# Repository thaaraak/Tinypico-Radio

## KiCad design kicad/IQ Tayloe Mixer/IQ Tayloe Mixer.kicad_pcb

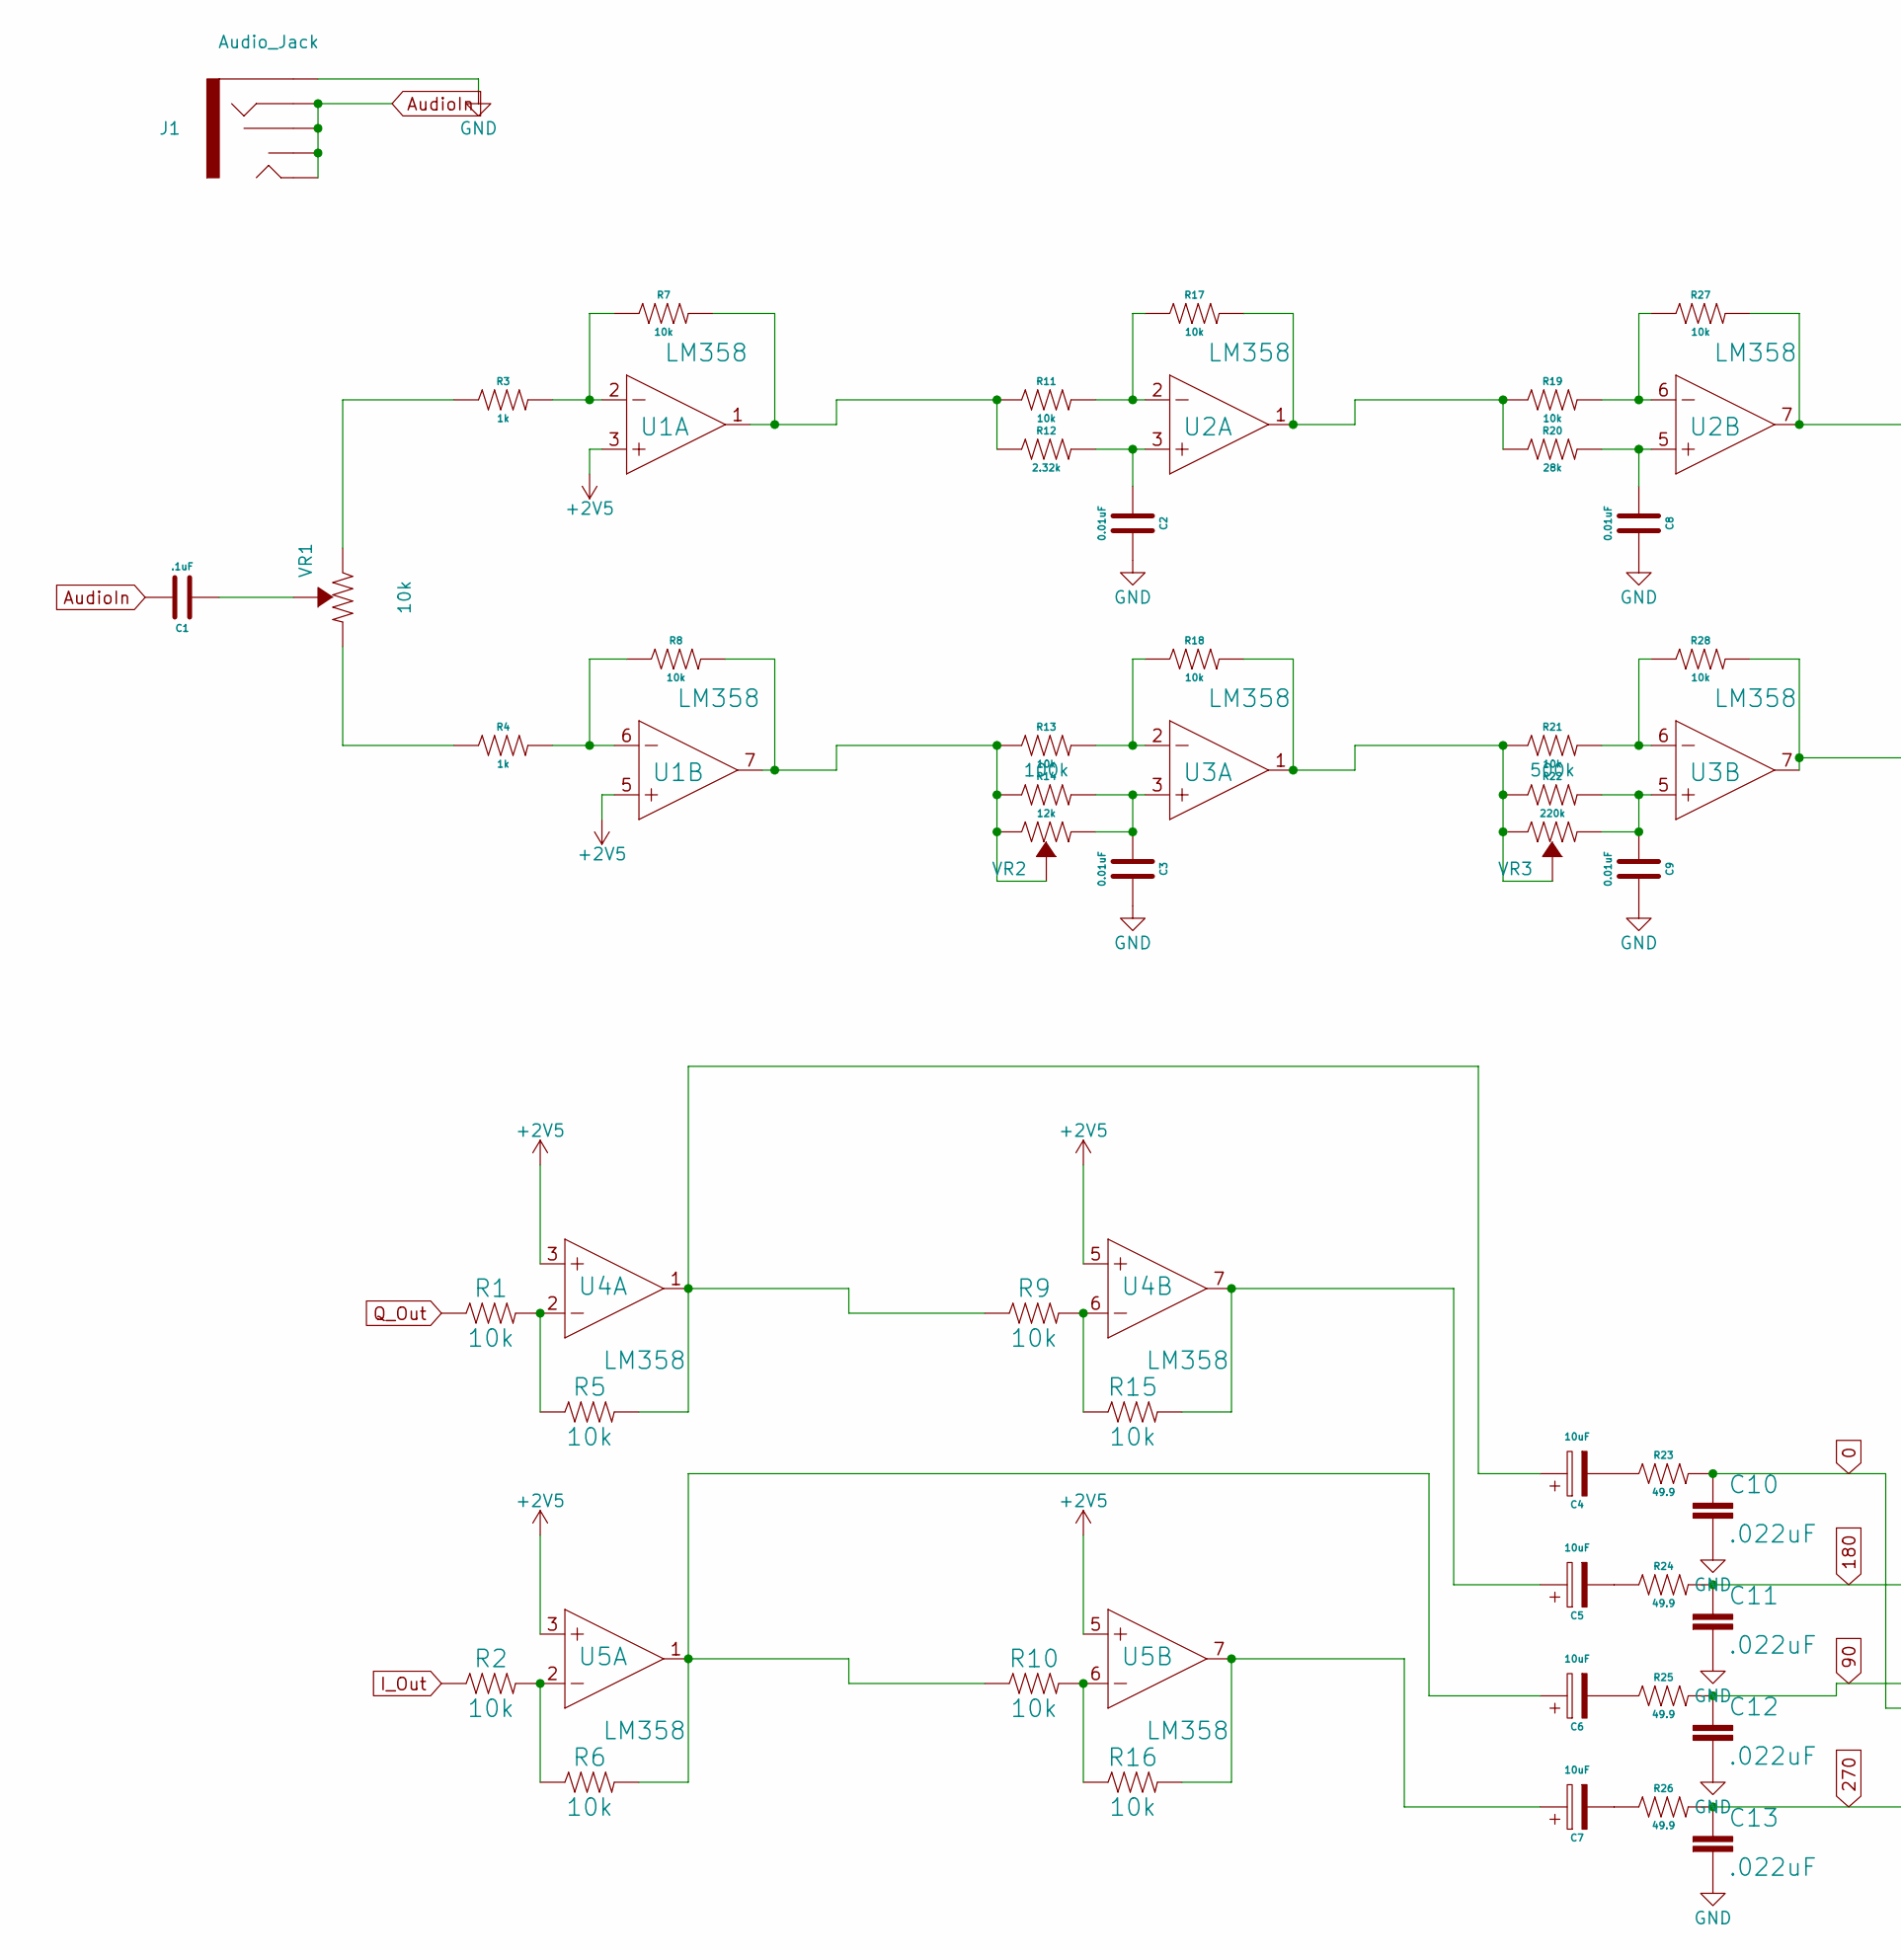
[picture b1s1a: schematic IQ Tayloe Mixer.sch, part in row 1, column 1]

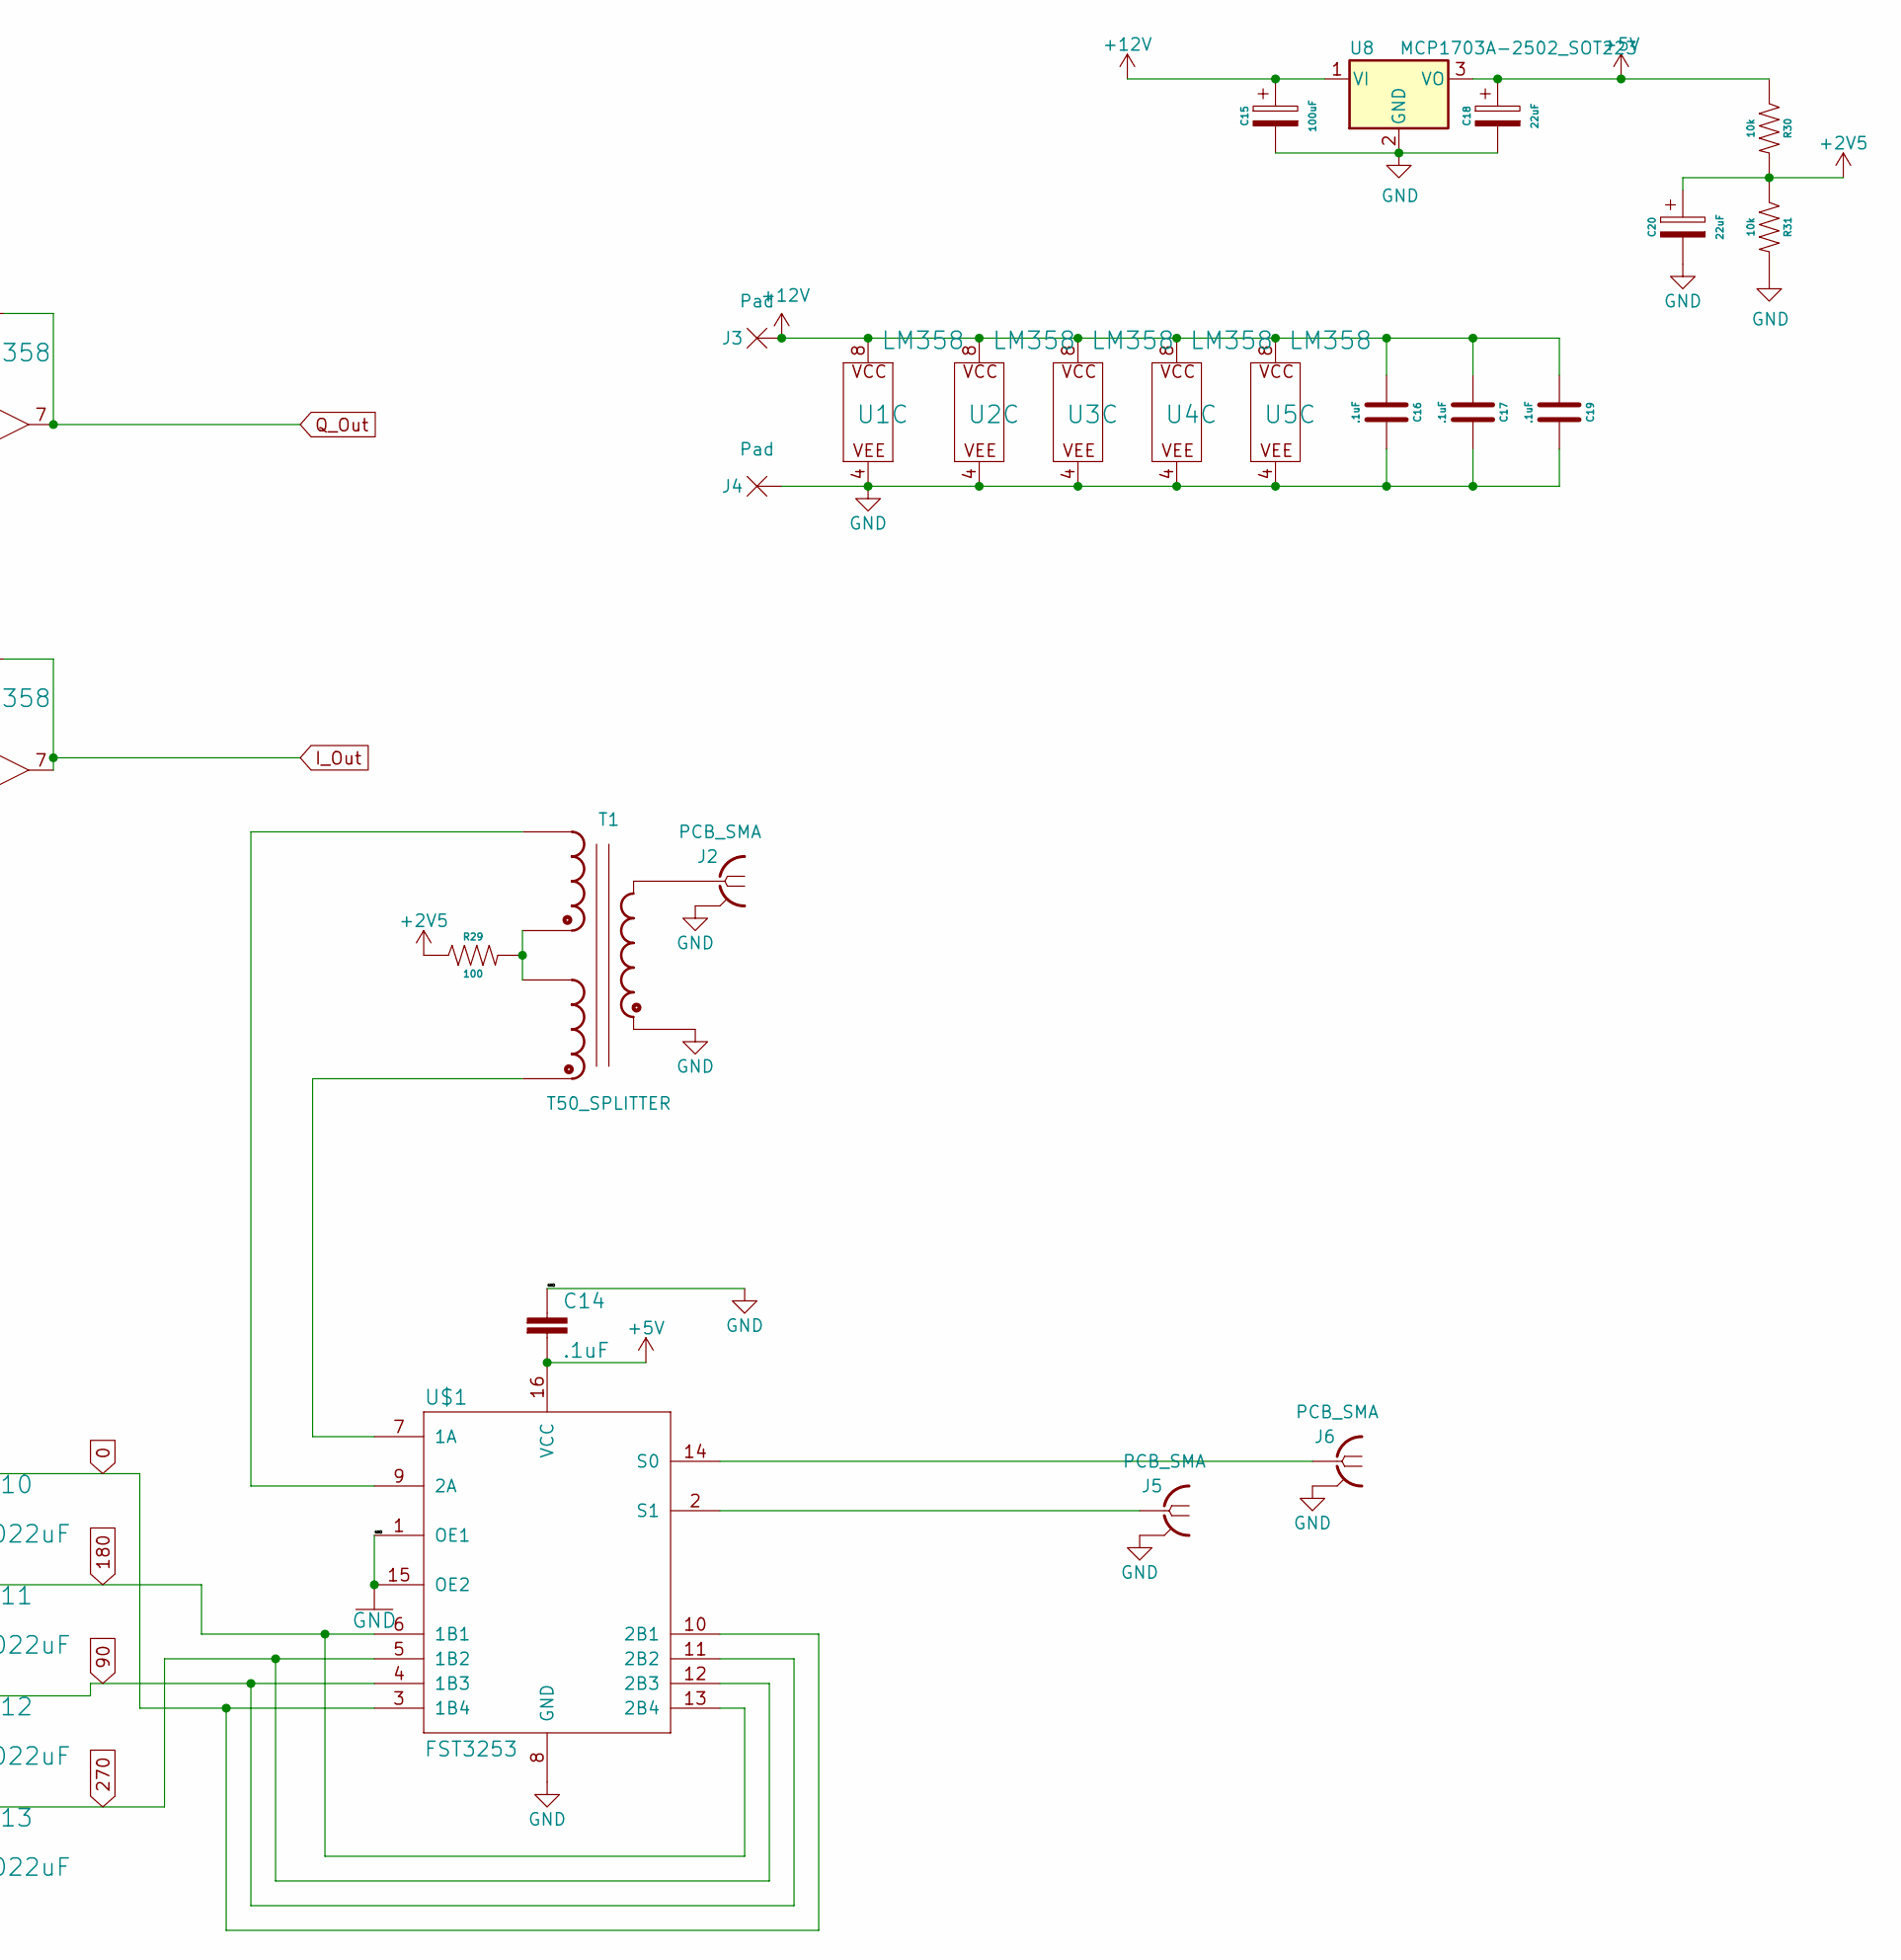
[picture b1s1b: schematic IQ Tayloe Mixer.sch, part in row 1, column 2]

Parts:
C1, C14, C16, C17, C19: .1uF; Capacitor 0805
C2, C3, C8, C9: 0.01uF; Capacitor 0805
C4, C5, C6, C7: 10uF; Cap_4x5.4
C10, C11, C12, C13: .022uF; Capacitor 1206
C15: 100uF; Cap_6.3x5.4
C18, C20: 22uF; Cap_4x5.4
J1: Audio_Jack
J2, J5, J6: PCB_SMA; PCB SMA
J3, J4: Pad
R1, R2, R5, R6, R7, R8, R9, R10, R11, R13, R15, R16, R17, R18, R19, R21, R27, R28, R30, R31: 10k; Resistor 0805
R3, R4: 1k; Resistor 0805
R12: 2.32k; Resistor 0805
R14: 12k; Resistor 0805
R20: 28k; Resistor 0805
R22: 220k; Resistor 0805
R23, R24, R25, R26: 49.9; Resistor 0805
R29: 100; Resistor 0805
T1: T50_SPLITTER; T50 Trifilar
U1, U2, U3, U4, U5: LM358; SO08
U8: MCP1703A-2502_SOT223; TO-252-3_TabPin2
U$1: FST3253; SO16
VR1: 10k; Trimpot
VR2: 100k; Trimpot
VR3: 500k; Trimpot

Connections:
0: C10.1, R23.2, U$1.3 (1B4), U$1.10 (2B1)
90: C12.1, R25.2, U$1.4 (1B3), U$1.11 (2B2)
180: C11.1, R24.2, U$1.6 (1B1), U$1.13 (2B4)
270: C13.1, R26.2, U$1.5 (1B2), U$1.12 (2B3)
+2V5: C20.1, R29.1, R30.2, R31.1, U1.3 (+IN), U1.5 (+IN), U4.3 (+IN), U4.5 (+IN), U5.3 (+IN), U5.5 (+IN)
+5V: C14.2, C18.1, R30.1, U8.3 (VO), U$1.16 (VCC)
+12V: C15.1, C16.1, C17.1, C19.1, J3.1, U1.8 (P$V+), U2.8 (P$V+), U3.8 (P$V+), U4.8 (P$V+), U5.8 (P$V+), U8.1 (VI)
AudioIn: C1.2, J1.RING, J1.RSH, J1.TIP, J1.TSH
GND: C2.2, C3.2, C8.2, C9.2, C10.2, C11.2, C12.2, C13.2, C14.1, C15.2, C16.2, C17.2, C18.2, C19.2, C20.2, J1.SLEEVE, J2.2, J2.3 (2), J2.4 (2), J2.5 (2), J4.1, J5.2, J5.3 (2), J5.4 (2), J5.5 (2), J6.2, J6.3 (2), J6.4 (2), J6.5 (2), R31.2, T1.C1B, U1.4 (P$V-), U2.4 (P$V-), U3.4 (P$V-), U4.4 (P$V-), U5.4 (P$V-), U8.2 (GND), U$1.1 (OE1), U$1.8 (GND), U$1.15 (OE2)
I_Out: R2.1, R28.2, U3.7 (OUT)
unnamed: C1.1, VR1.2 (WIPER)
unnamed: C2.1, R12.2, U2.3 (+IN)
unnamed: C3.1, R14.2, U3.3 (+IN), VR2.3 (CCW)
unnamed: C4.1, R5.2, R9.1, U4.1 (OUT)
unnamed: C4.2, R23.1
unnamed: C5.1, R15.2, U4.7 (OUT)
unnamed: C5.2, R24.1
unnamed: C6.1, R6.2, R10.1, U5.1 (OUT)
unnamed: C6.2, R25.1
unnamed: C7.1, R16.2, U5.7 (OUT)
unnamed: C7.2, R26.1
unnamed: C8.1, R20.2, U2.5 (+IN)
unnamed: C9.1, R22.2, U3.5 (+IN), VR3.3 (CCW)
unnamed: J2.1, T1.C1A
unnamed: J5.1, U$1.2 (S1)
unnamed: J6.1, U$1.14 (S0)
unnamed: R1.2, R5.1, U4.2 (-IN)
unnamed: R2.2, R6.1, U5.2 (-IN)
unnamed: R3.1, VR1.1 (CW)
unnamed: R3.2, R7.1, U1.2 (-IN)
unnamed: R4.1, VR1.3 (CCW)
unnamed: R4.2, R8.1, U1.6 (-IN)
unnamed: R10.2, R16.1, U5.6 (-IN)
unnamed: R7.2, R11.1, R12.1, U1.1 (OUT)
unnamed: R11.2, R17.1, U2.2 (-IN)
unnamed: R8.2, R13.1, R14.1, U1.7 (OUT), VR2.1 (CW), VR2.2 (WIPER)
unnamed: R13.2, R18.1, U3.2 (-IN)
unnamed: R9.2, R15.1, U4.6 (-IN)
unnamed: R17.2, R19.1, R20.1, U2.1 (OUT)
unnamed: R18.2, R21.1, R22.1, U3.1 (OUT), VR3.1 (CW), VR3.2 (WIPER)
unnamed: R19.2, R27.1, U2.6 (-IN)
unnamed: R21.2, R28.1, U3.6 (-IN)
unnamed: R29.2, T1.C2A, T1.C3B
unnamed: T1.C2B, U$1.7 (1A)
unnamed: T1.C3A, U$1.9 (2A)
Q_Out: R1.1, R27.2, U2.7 (OUT)

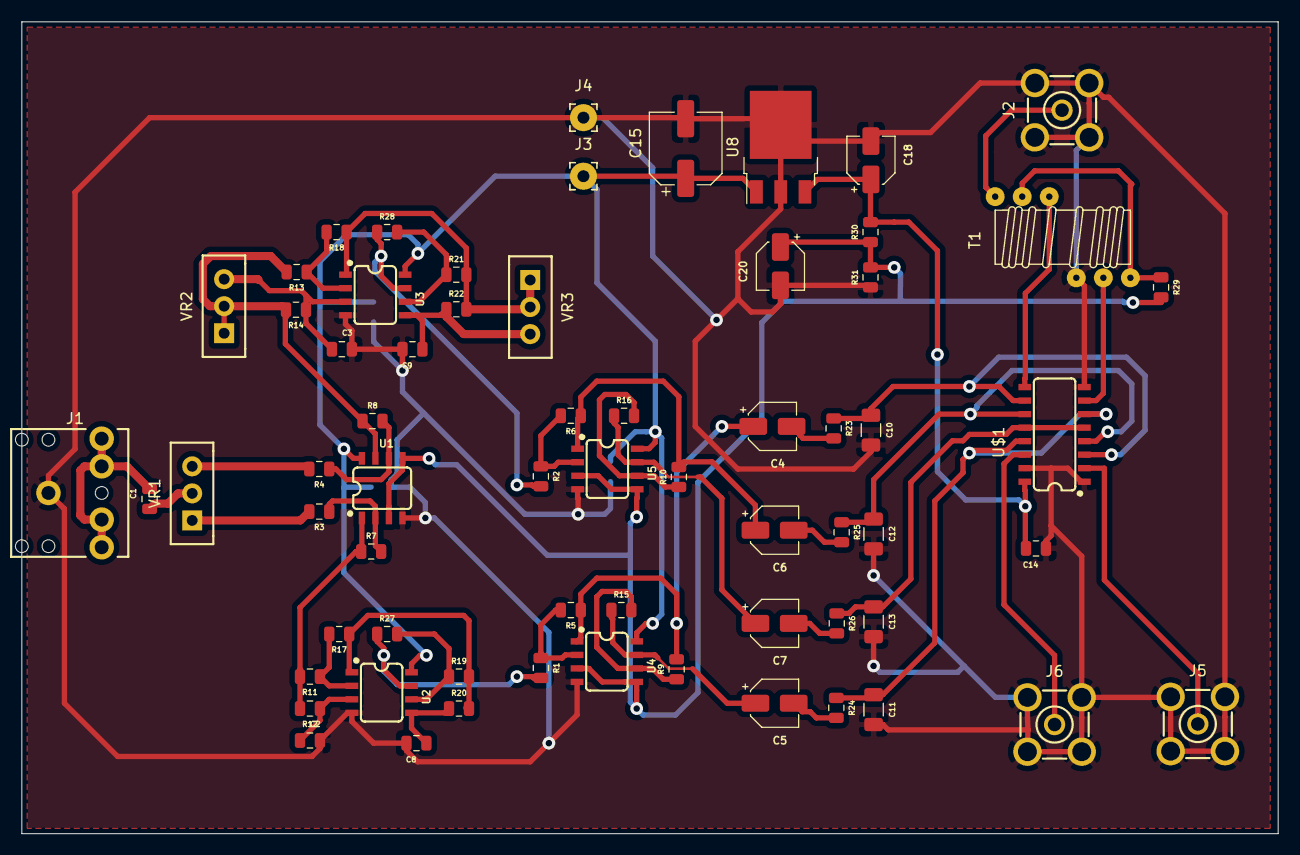
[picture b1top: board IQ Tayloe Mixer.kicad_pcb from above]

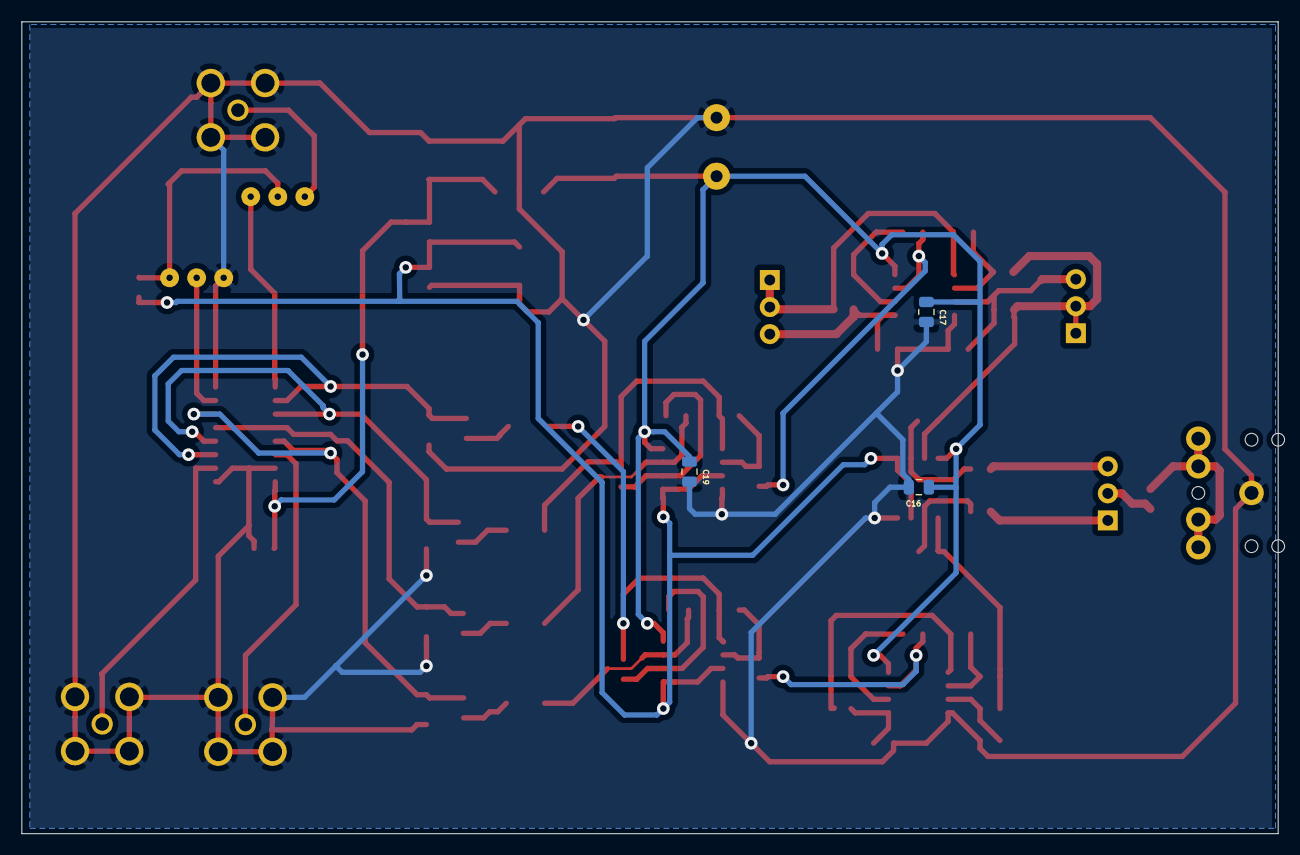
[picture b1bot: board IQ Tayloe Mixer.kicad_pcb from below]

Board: 2 copper layers, 118.0 x 76.2 mm, 68 parts (3 on the bottom side), 46 nets.

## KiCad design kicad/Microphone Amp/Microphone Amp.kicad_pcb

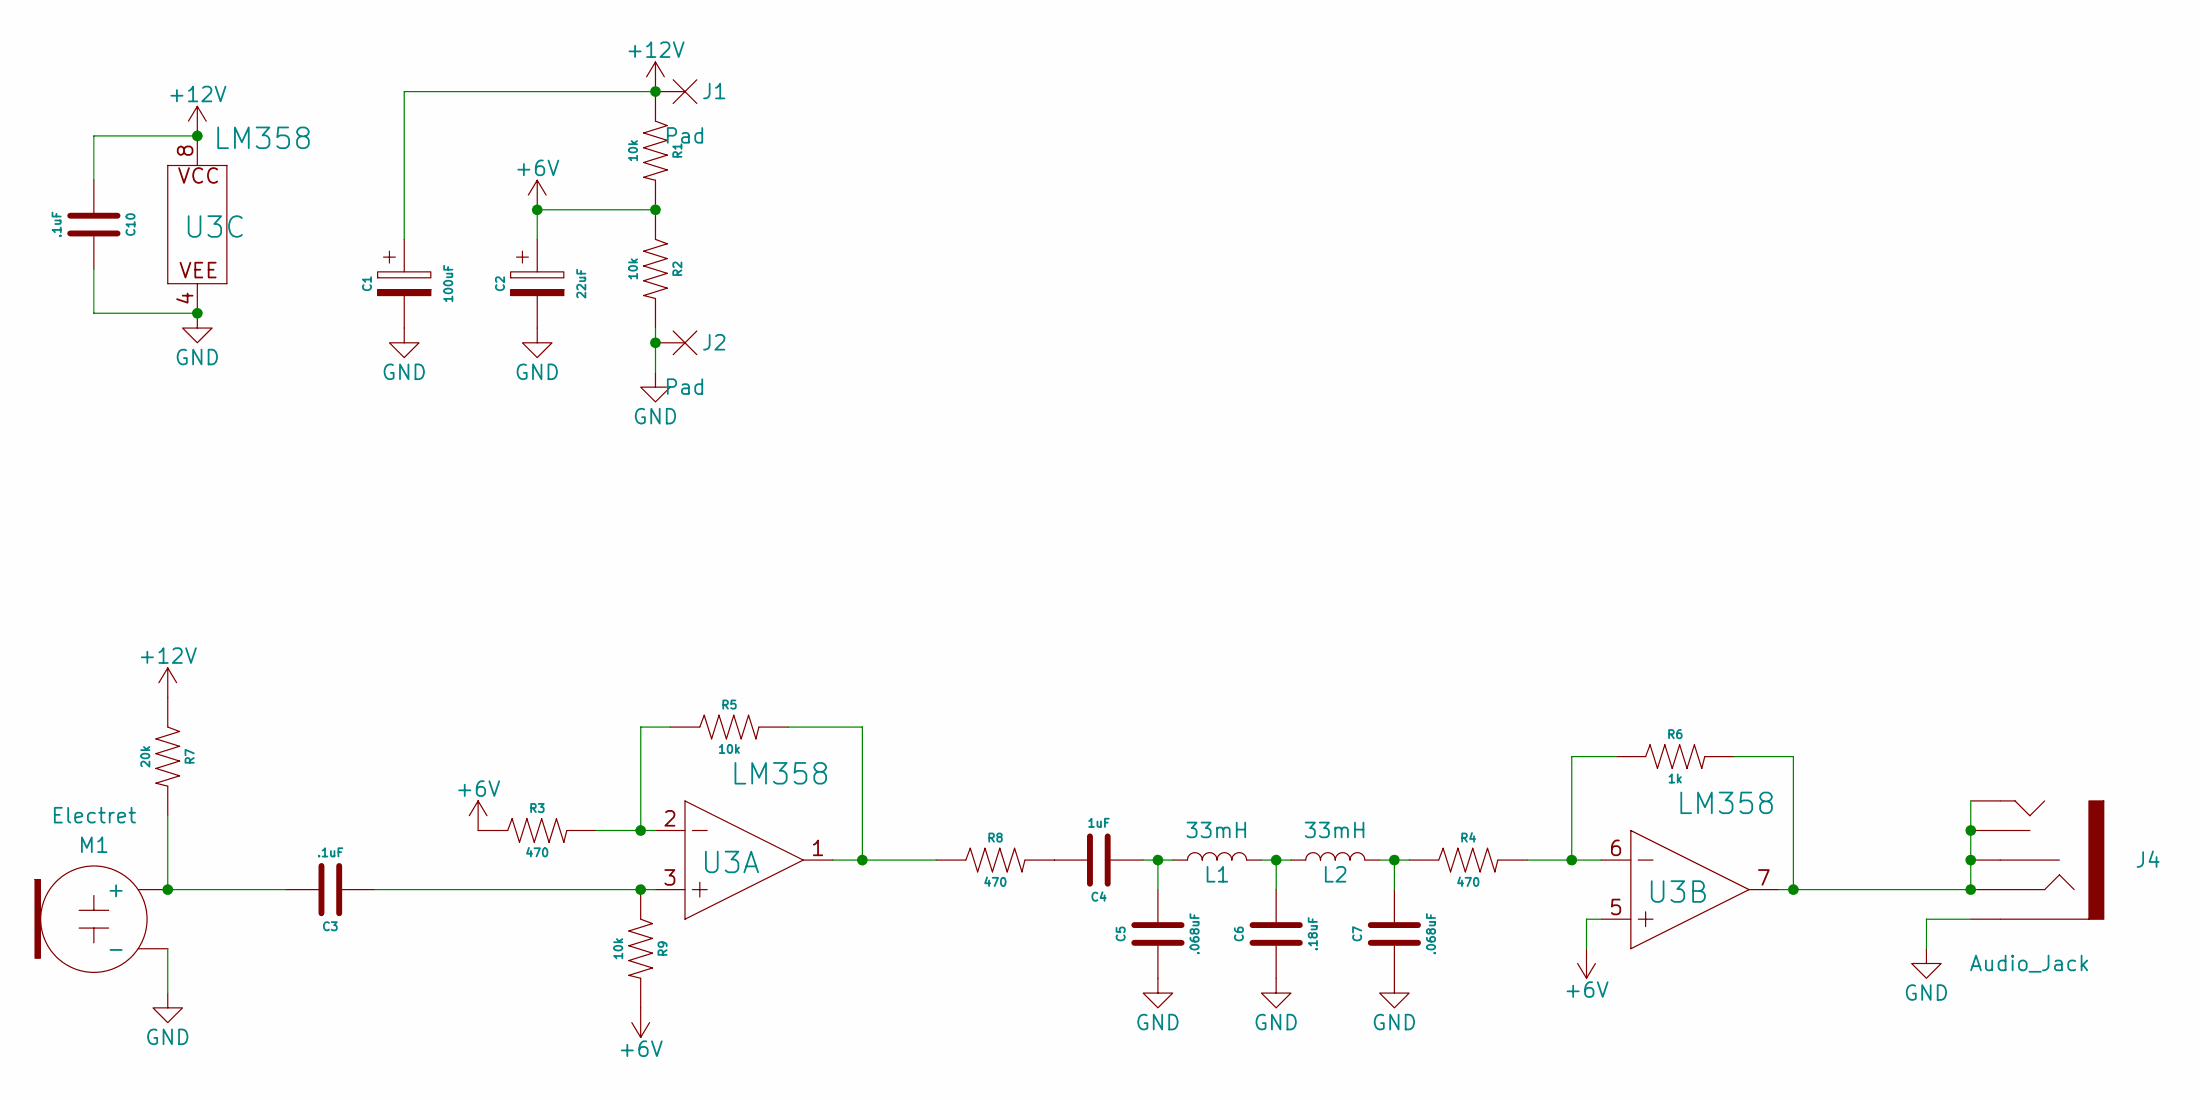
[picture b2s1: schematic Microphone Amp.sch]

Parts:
C1: 100uF; Cap_6.3x5.4
C2: 22uF; Cap_4x5.4
C3, C10: .1uF; Capacitor 0805
C4: 1uF; Capacitor 0805
C5, C7: .068uF; Capacitor 1206
C6: .18uF; Capacitor 1206
J1, J2: Pad
J4: Audio_Jack
L1, L2: 33mH; Inductor_5mm
M1: Electret
R1, R2, R5, R9: 10k; Resistor 0805
R3, R4, R8: 470; Resistor 0805
R6: 1k; Resistor 0805
R7: 20k; Resistor 0805
U3: LM358; SO08

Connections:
+6V: C2.1, R1.2, R2.1, R3.1, R9.2, U3.5 (+IN)
+12V: C1.1, C10.1, J1.1, R1.1, R7.1, U3.8 (P$V+)
GND: C1.2, C2.2, C5.1, C6.1, C7.1, C10.2, J2.1, J4.SLEEVE, M1.2 (-), R2.2, U3.4 (P$V-)
unnamed: C3.1, R9.1, U3.3 (+IN)
unnamed: C3.2, M1.1 (+), R7.2
unnamed: C4.1, C5.2, L1.1
unnamed: C4.2, R8.2
unnamed: C6.2, L1.2, L2.1
unnamed: C7.2, L2.2, R4.1
unnamed: J4.RING, J4.RSH, J4.TIP, J4.TSH, R6.2, U3.7 (OUT)
unnamed: R3.2, R5.1, U3.2 (-IN)
unnamed: R4.2, R6.1, U3.6 (-IN)
unnamed: R5.2, R8.1, U3.1 (OUT)

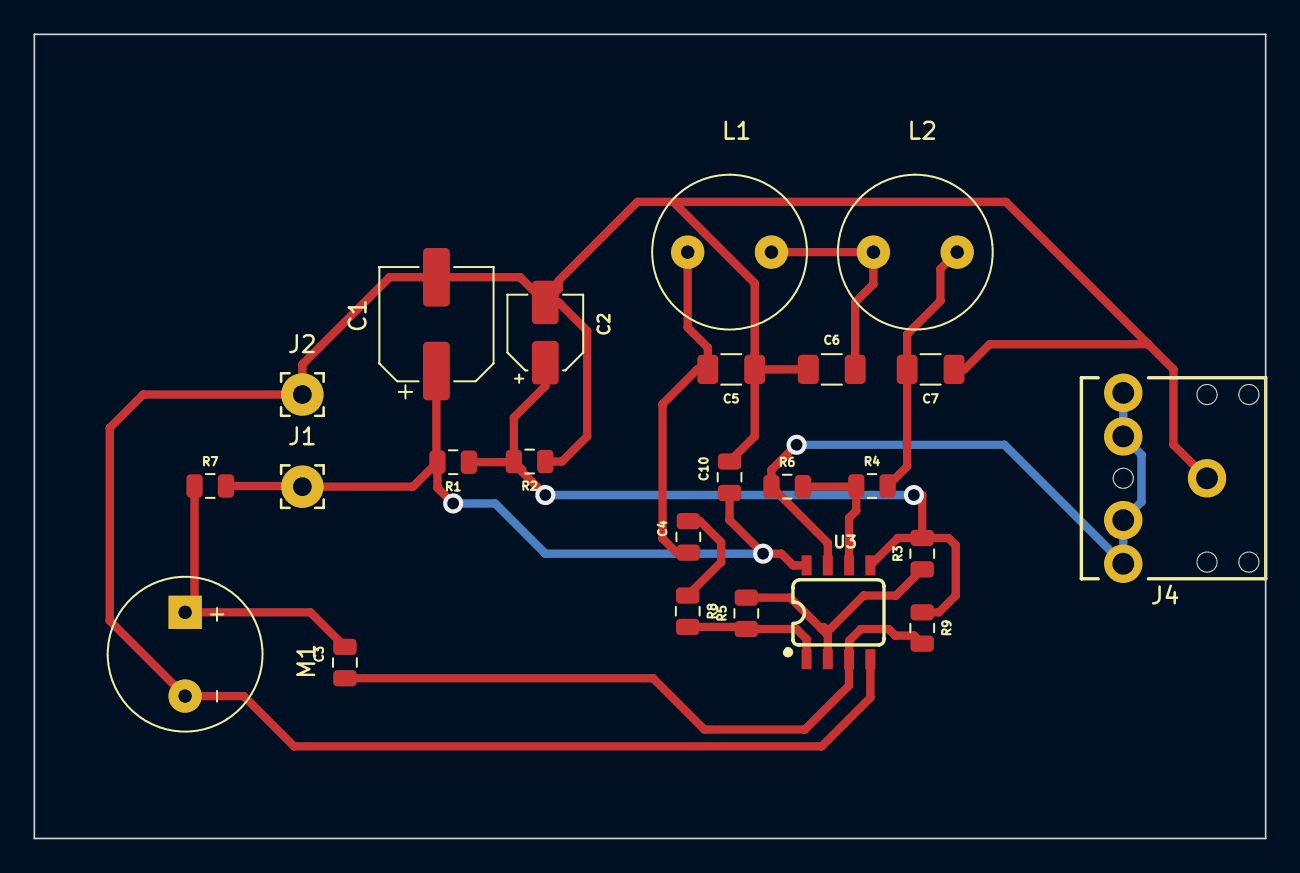
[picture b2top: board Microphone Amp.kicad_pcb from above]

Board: 2 copper layers, 73.5 x 48.0 mm, 24 parts (0 on the bottom side), 13 nets.

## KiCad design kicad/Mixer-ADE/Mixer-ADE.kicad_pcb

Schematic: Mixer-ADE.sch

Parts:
C1, C2: 100uF; CPOL-RADIAL-2.5MM-5MM
C3, C5: 1uF; CAP-PTH-5MM
C4, C10: 47nF; CAP-PTH-5MM
C6, C7: 680nF; CAP-PTH-5MM
C8, C9: 220pF; CAP-PTH-5MM
J1: Audio_Jack
J2, J3, J6: BNC
M1, M2: ADEX-10L
R1, R8: 51; R_Axial_DIN0204_L3.6mm_D1.6mm_P2.54mm_Vertical
R2, R15: 3.3k; R_Axial_DIN0204_L3.6mm_D1.6mm_P2.54mm_Vertical
R3, R4: 50; R_Axial_DIN0204_L3.6mm_D1.6mm_P2.54mm_Vertical
R5: 100; R_Axial_DIN0204_L3.6mm_D1.6mm_P2.54mm_Vertical
R6, R7: 47; R_Axial_DIN0204_L3.6mm_D1.6mm_P2.54mm_Vertical
R9, R10, R13, R14: 150; R_Axial_DIN0204_L3.6mm_D1.6mm_P2.54mm_Vertical
R11, R12: 30; R_Axial_DIN0204_L3.6mm_D1.6mm_P2.54mm_Vertical
T1: T50_SPLITTER; T50 Trifilar

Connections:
GND: C3.2, C5.2, C6.2, C7.2, C8.2, C9.2, J1.SLEEVE, J2.GND, J3.GND, J6.GND, M1.1 (GND), M1.4 (GND), M1.5 (GND), M2.1 (GND), M2.4 (GND), M2.5 (GND), R5.1, R9.1, R10.1, R13.2, R14.2, T1.C1B
I_IN: J1.TIP, J1.TSH, R4.1
unnamed: C1.1, R3.2
unnamed: C1.2, R6.1
unnamed: C2.1, R4.2
unnamed: C2.2, R7.1
unnamed: C3.1, R1.2, R6.2, R9.2, R11.1
unnamed: C4.1, R2.2
unnamed: C4.2, J2.S (OUT)
unnamed: C5.1, R7.2, R8.2, R10.2, R12.1
unnamed: C6.1, R1.1
unnamed: C7.1, R8.1
unnamed: C8.1, M1.2 (IF), R11.2, R13.1
unnamed: C9.1, M2.2 (IF), R12.2, R14.1
unnamed: C10.1, R15.2
unnamed: C10.2, J3.S (OUT)
unnamed: J6.S (OUT), T1.C1A
unnamed: M1.3 (RF), T1.C3A
unnamed: M1.6 (LO), R2.1
unnamed: M2.3 (RF), T1.C2B
unnamed: M2.6 (LO), R15.1
unnamed: R5.2, T1.C2A, T1.C3B
Q_IN: J1.RING, J1.RSH, R3.1

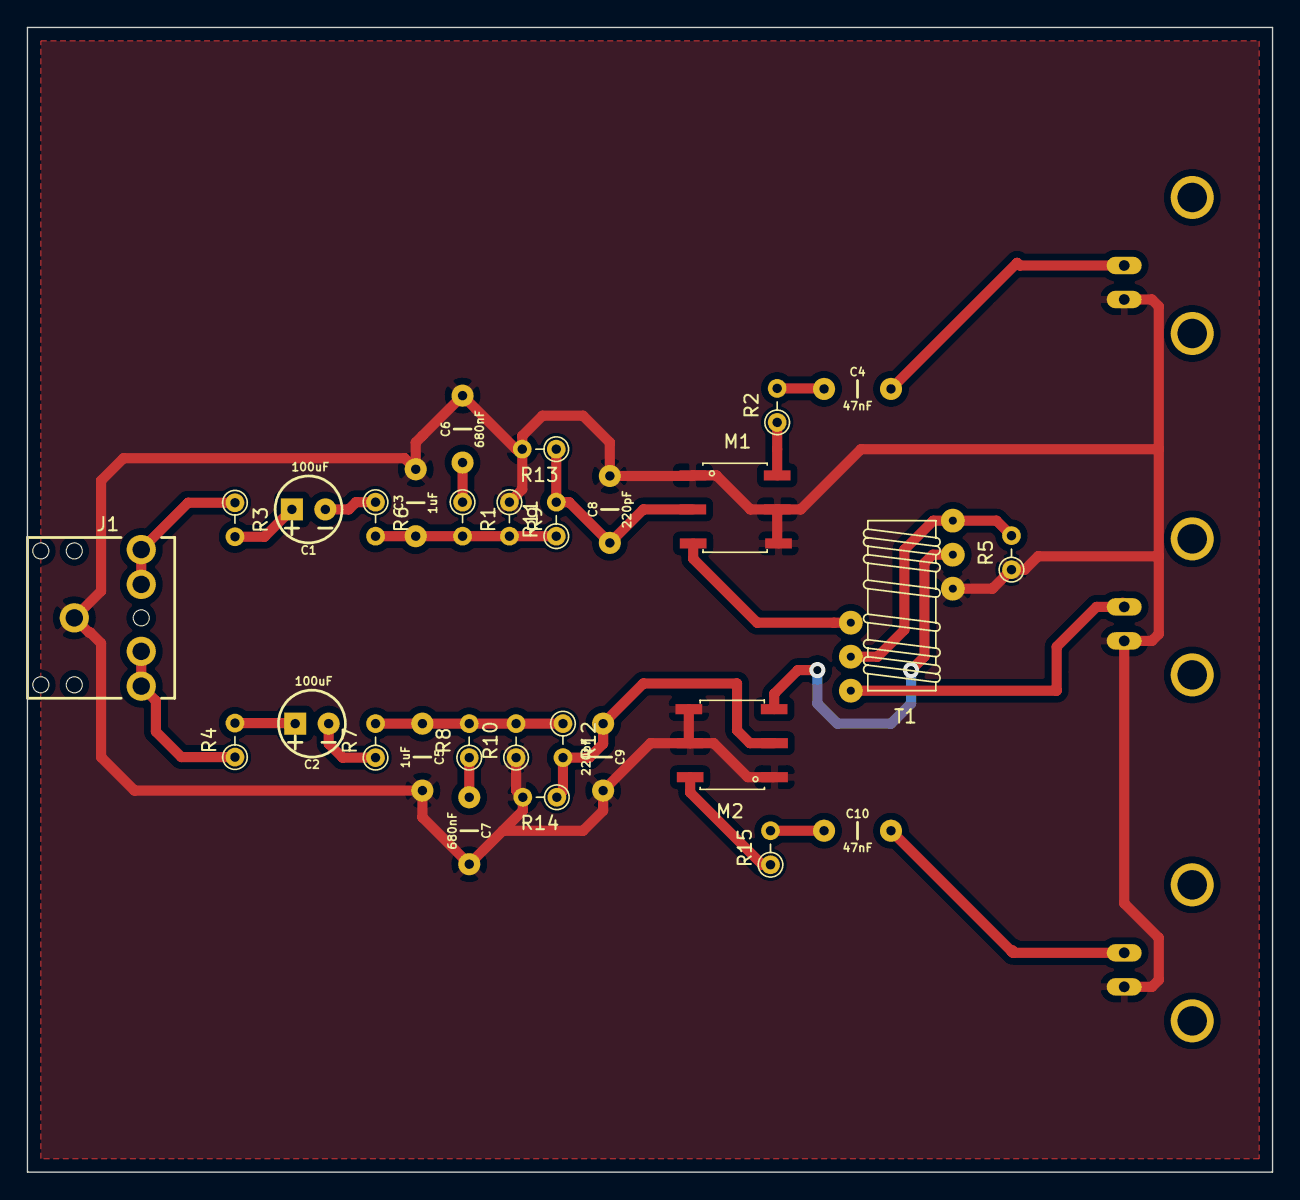
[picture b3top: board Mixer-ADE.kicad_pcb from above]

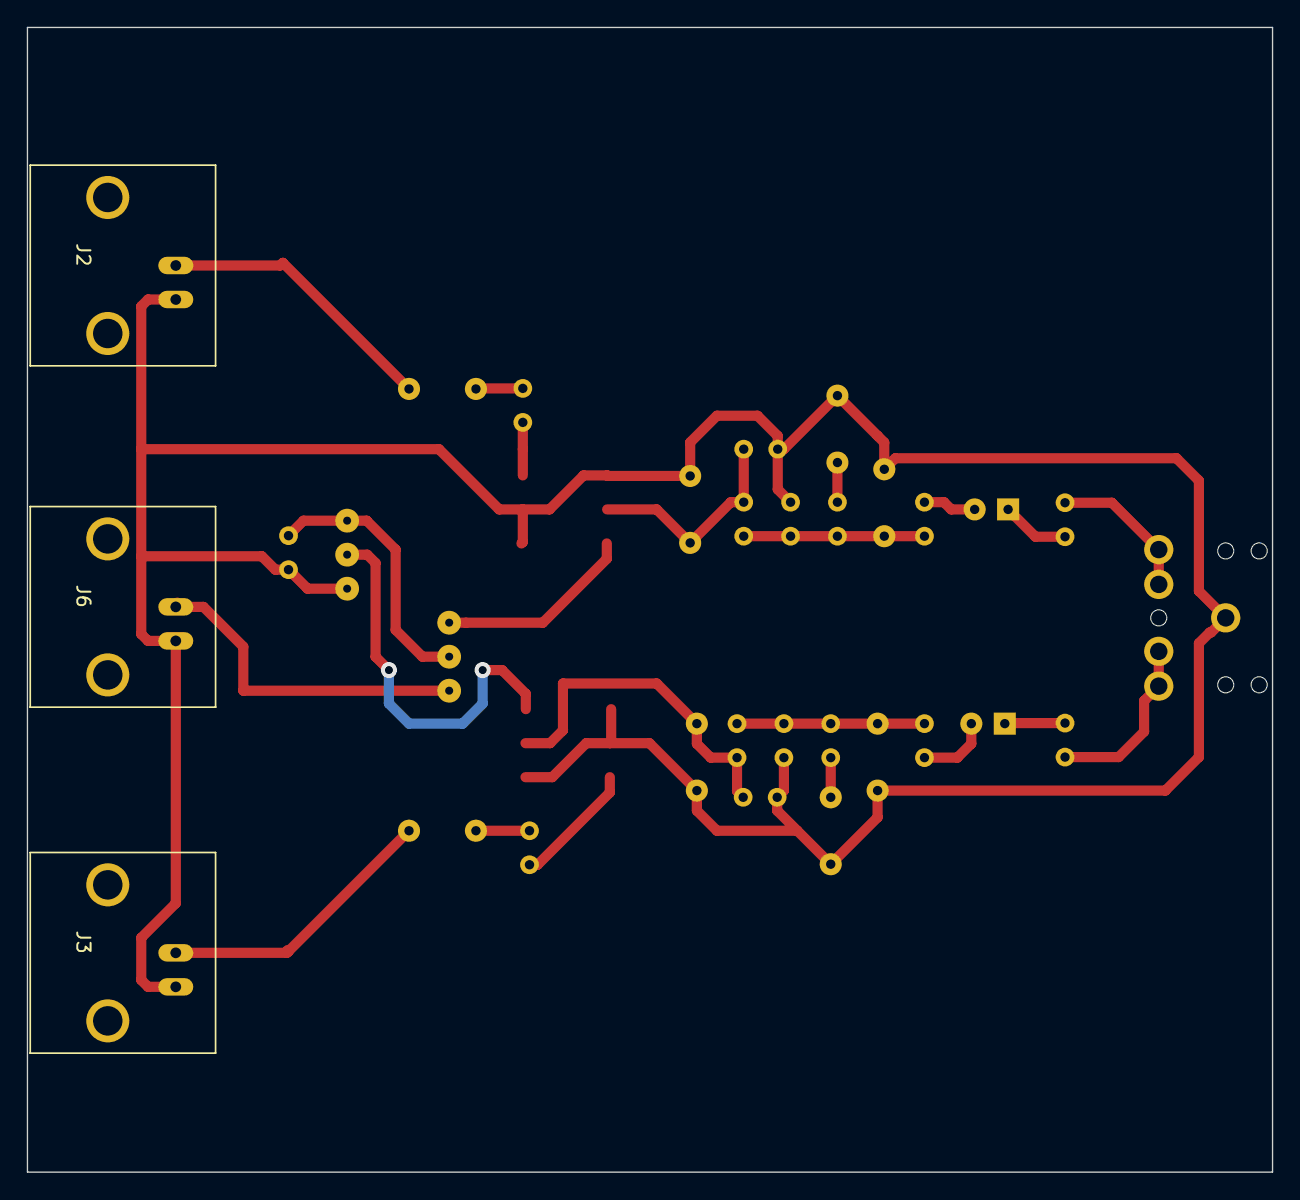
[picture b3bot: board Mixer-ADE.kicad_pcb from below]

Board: 2 copper layers, 93.0 x 85.5 mm, 32 parts (3 on the bottom side), 23 nets.
